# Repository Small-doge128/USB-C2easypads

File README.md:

# about
A really small, compact and simple USB-C PCB with 2 output pads and of course USB-C (16pin). It's for 12V (47k resistor), but if you want higher voltage, buy a different Rset resistor, TVS diodes and fuse.  [onshape](https://cad.onshape.com/documents/7232de9fd70225e34f9573ad/w/c2cc3483bf6da956bf569f6e/e/ac040c47bc44097746a4bcaa)

# features
USB-C 16 pin, 2 output pads, 4 resistors, 1 poly fuse, CH221K for higher voltage, 10uf capacitor and 100nf capacitor. All bundled up on a small PCB that I designed in Kicad. If you want you can have higher voltage or lower, all you need to do is change the fuse, TVS diodes and Rset resistor. The target voltage can be easily set by a table on the back of the PCB and a arrow pointing to the Rset resistor.

# dimensions
PCB - 22.75 mm x 10.75 mm

# why did I create it
I wanted a way to convert my soldering iron to USB-C for better usability, so I thought why not make it for more use and for more people, so that's how it was created.

# demo video:

# pictures

# BOM

| Name | Purpose | Qty | Price (USD) | Distributor | Link |
| :--- | :--- | :---: | :---: | :--- | :--- |
| PCB | for conecting all of the parts | 5 | $ 5 | PCBWAY | [Link](https://pcbway.com) |
| CH221K chip | for drawing more power from the USB-C | 5 | $ 1.65 | LCSC | [Link](https://www.lcsc.com/product-detail/C5125736.html) |
| TVS diode | for protection | 10 | $ 0.06 | LCSC | [Link](https://www.lcsc.com/product-detail/C7018346.html) |
| polyfuse | for protecting all of the parts from over-current / short circuits | 20 | $ 0.69 | LCSC | [Link](https://www.lcsc.com/product-detail/C42449089.html) |
| 47kΩ resistor | for drawing the requested voltage | 100 | $ 1.31 | LCSC | [Link](https://www.lcsc.com/product-detail/C17713.html) |
| 1kΩ resistor | protection | 100 | already at home | LCSC | [Link](https://www.lcsc.com/product-detail/C84375.html) |
| 5.1kΩ resistor | protection | 200 | already at home | LCSC | [Link](https://www.lcsc.com/product-detail/C95781.html) |
| 10uf capacitor | protection | 100 | already at home | LCSC | [Link](https://www.lcsc.com/product-detail/C13585.html) |
| 100nf capacitor | protection | 100 | already at home | LCSC | [Link](https://www.lcsc.com/product-detail/C49678.html) |
| **TOTAL without shipping and taxes** | | | **$ 8.71** | | |
| **TOTAL with shipping and taxes** | | | **$ 43** | | |

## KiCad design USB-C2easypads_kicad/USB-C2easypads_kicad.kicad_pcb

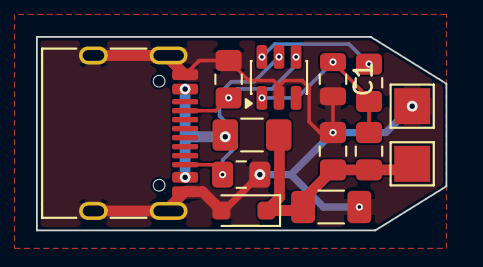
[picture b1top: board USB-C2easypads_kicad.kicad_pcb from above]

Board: 2 copper layers, 22.8 x 10.8 mm, 13 parts (0 on the bottom side), 7 nets.

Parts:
C1: C_Small; C_0805_2012Metric
C2: C_Small; C_0805_2012Metric_Pad1.18x1.45mm_HandSolder
C3: C_Small; C_1206_3216Metric_Pad1.33x1.80mm_HandSolder
D1: HSD12C; D_SOD-323_HandSoldering
F1: 3A; Fuse_1206_3216Metric_Pad1.42x1.75mm_HandSolder
J1: USB_C_Receptacle_USB2.0_16P; USB_C_Receptacle_HRO_TYPE-C-31-M-12
J2, J3: Conn_01x01_Pin; TestPoint_Pad_2.0x2.0mm
R2, R3, R4, R5: R; C_0805_2012Metric_Pad1.18x1.45mm_HandSolder
U1: CH221K; SOT-23-6

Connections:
/CC1: J1.A5 (CC1), R4.2, U1.4 (CC1)
/CC2: J1.B5 (CC2), R5.2, U1.5 (CC2)
/USB_VBUS: F1.1, J1.A4 (VBUS), J1.A9 (VBUS), J1.B4 (VBUS), J1.B9 (VBUS)
GND: C1.2, C2.1, C3.2, D1.2 (A), J1.A1 (GND), J1.A12 (GND), J1.B1 (GND), J1.B12 (GND), J1.SH (SHIELD), J2.1 (Pin_1_1), R4.1, R5.1, U1.2 (GND)
unnamed: R2.1, U1.6 (CFG)
unnamed: C1.1, R2.2, R3.1, U1.1 (VDD)
VBUS: C2.2, C3.1, D1.1 (K), F1.2, J3.1 (Pin_1_1), R3.2
